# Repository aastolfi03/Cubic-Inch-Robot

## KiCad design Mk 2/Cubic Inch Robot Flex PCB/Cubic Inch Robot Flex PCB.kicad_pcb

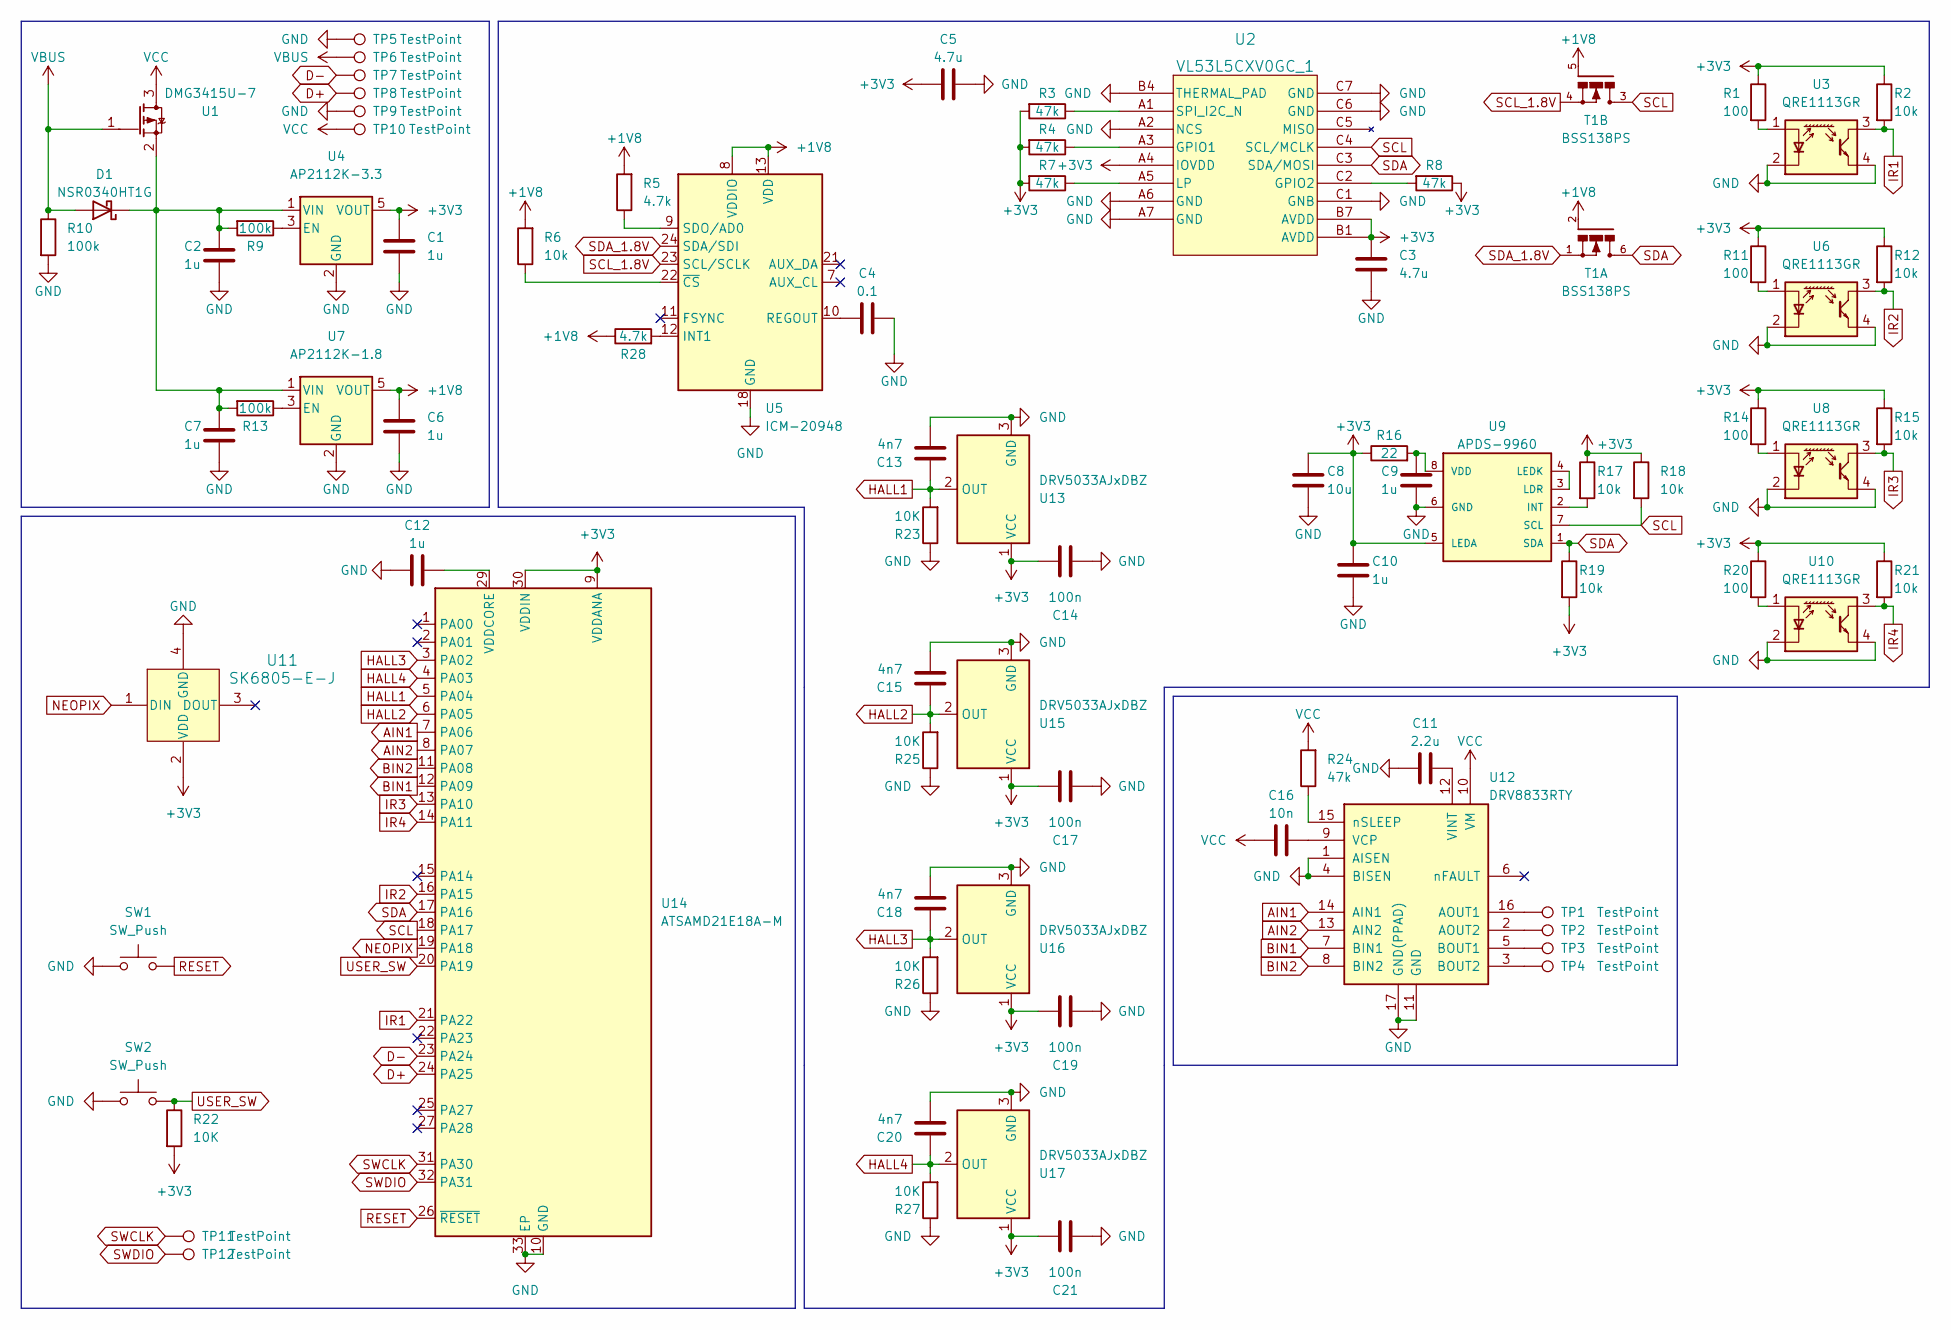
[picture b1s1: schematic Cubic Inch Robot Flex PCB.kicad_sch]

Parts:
C1, C2, C6, C7, C9, C10, C12: 1u; C_0603_1608Metric
C3, C5: 4.7u; C_0603_1608Metric
C4: 0.1; C_0603_1608Metric
C8: 10u; C_0603_1608Metric
C11: 2.2u; C_0603_1608Metric
C13, C15, C18, C20: 4n7; C_0603_1608Metric
C14, C17, C19, C21: 100n; C_0603_1608Metric
C16: 10n; C_0603_1608Metric
D1: NSR0340HT1G; D_SOD-323
R1, R11, R14, R20: 100; R_0603_1608Metric
R2, R6, R12, R15, R17, R18, R19, R21: 10k; R_0603_1608Metric
R3, R4, R7, R8, R24: 47k; R_0603_1608Metric
R5, R28: 4.7k; R_0603_1608Metric
R9, R10, R13: 100k; R_0603_1608Metric
R16: 22; R_0603_1608Metric
R22, R23, R25, R26, R27: 10K; R_0603_1608Metric
SW1, SW2: SW_Push; SW_Push_SPST_NO_Alps_SKRK
T1: BSS138PS; SOT363
TP1, TP2, TP3, TP4, TP5, TP6, TP7, TP8, TP9, TP10, TP11, TP12: TestPoint; TestPoint_Pad_D1.0mm
U1: DMG3415U-7; SOT95P240X105-3N; MPN DMG3415U-7
U2: VL53L5CXV0GC_1; LGA_CXV0GC&slash_1_STM
U3, U6, U8, U10: QRE1113GR; OnSemi_CASE100CY
U4: AP2112K-3.3; SOT-23-5
U5: ICM-20948; InvenSense_QFN-24_3x3mm_P0.4mm
U7: AP2112K-1.8; SOT-23-5
U9: APDS-9960
U11: SK6805-E-J; 4492_ADA
U12: DRV8833RTY; Texas_S-PWQFN-N16_EP2.1x2.1mm_ThermalVias
U13, U15, U16, U17: DRV5033AJxDBZ; SOT-23
U14: ATSAMD21E18A-M; QFN-32-1EP_5x5mm_P0.5mm_EP3.6x3.6mm

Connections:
+1V8: C6.1, R5.2, R6.2, R28.1, T1.2, T1.5, U5.8 (VDDIO), U5.13 (VDD), U7.5 (VOUT)
+3V3: C1.1, C3.1, C5.1, C8.1, C10.1, C14.2, C17.2, C19.2, C21.2, R1.1, R2.1, R3.2, R4.2, R7.2, R8.1, R11.1, R12.1, R14.1, R15.1, R16.1, R17.1, R18.1, R19.2, R20.1, R21.1, R22.2, U2.A4 (IOVDD), U2.B1 (AVDD), U2.B7 (AVDD), U4.5 (VOUT), U9.5 (LEDA), U11.2 (VDD), U13.1 (VCC), U14.9 (VDDANA), U14.30 (VDDIN), U15.1 (VCC), U16.1 (VCC), U17.1 (VCC)
AIN1: U12.14 (AIN1), U14.7 (PA06)
AIN2: U12.13 (AIN2), U14.8 (PA07)
BIN1: U12.7 (BIN1), U14.12 (PA09)
BIN2: U12.8 (BIN2), U14.11 (PA08)
D+: TP8.1, U14.24 (PA25)
D-: TP7.1, U14.23 (PA24)
GND: C1.2, C2.2, C3.2, C4.2, C5.2, C6.2, C7.2, C8.2, C9.2, C10.2, C11.1, C12.1, C13.2, C14.1, C15.2, C17.1, C18.2, C19.1, C20.2, C21.1, R10.2, R23.1, R25.1, R26.1, R27.1, SW1.1, SW2.1, TP5.1, TP9.1, U2.A2 (NCS), U2.A6 (GND), U2.A7 (GND), U2.B4 (THERMAL_PAD), U2.C1 (GNB), U2.C6 (GND), U2.C7 (GND), U3.2 (K), U3.4, U4.2 (GND), U5.18 (GND), U5.20 (GND), U6.2 (K), U6.4, U7.2 (GND), U8.2 (K), U8.4, U9.6 (GND), U10.2 (K), U10.4, U11.4 (GND), U12.1 (AISEN), U12.4 (BISEN), U12.11 (GND), U12.17 (GND(PPAD)), U13.3 (GND), U14.10 (GND), U14.28 (GND), U14.33 (EP), U15.3 (GND), U16.3 (GND), U17.3 (GND)
HALL1: C13.1, R23.2, U13.2 (OUT), U14.5 (PA04)
HALL2: C15.1, R25.2, U14.6 (PA05), U15.2 (OUT)
HALL3: C18.1, R26.2, U14.3 (PA02), U16.2 (OUT)
HALL4: C20.1, R27.2, U14.4 (PA03), U17.2 (OUT)
IR1: R2.2, U3.3, U14.21 (PA22)
IR2: R12.2, U6.3, U14.16 (PA15)
IR3: R15.2, U8.3, U14.13 (PA10)
IR4: R21.2, U10.3, U14.14 (PA11)
NEOPIX: U11.1 (DIN), U14.19 (PA18)
unnamed: C2.1, C7.1, D1.1 (K), R9.2, R13.2, U1.2, U4.1 (VIN), U7.1 (VIN)
unnamed: C4.1, U5.10 (REGOUT)
unnamed: C9.1, R16.2, U9.8 (VDD)
unnamed: C11.2, U12.12 (VINT)
unnamed: C12.2, U14.29 (VDDCORE)
unnamed: C16.2, U12.9 (VCP)
unnamed: R1.2, U3.1 (A)
unnamed: R3.1, U2.A1 (SPI_I2C_N)
unnamed: R4.1, U2.A3 (GPIO1)
unnamed: R5.1, U5.9 (SDO/AD0)
unnamed: R6.1, U5.22 (~CS)
unnamed: R7.1, U2.A5 (LP)
unnamed: R8.2, U2.C2 (GPIO2)
unnamed: R9.1, U4.3 (EN)
unnamed: R11.2, U6.1 (A)
unnamed: R13.1, U7.3 (EN)
unnamed: R14.2, U8.1 (A)
unnamed: R17.2, U9.2 (INT)
unnamed: R20.2, U10.1 (A)
unnamed: R24.1, U12.15 (nSLEEP)
unnamed: R28.2, U5.12 (INT1)
unnamed: TP1.1, U12.16 (AOUT1)
unnamed: TP2.1, U12.2 (AOUT2)
unnamed: TP3.1, U12.5 (BOUT1)
unnamed: TP4.1, U12.3 (BOUT2)
unnamed: U9.3 (LDR), U9.4 (LEDK)
RESET: SW1.2, U14.26 (~RESET)
SCL: R18.2, T1.3, U2.C4 (SCL/MCLK), U9.7 (SCL), U14.18 (PA17)
SCL_1.8V: T1.4, U5.23 (SCL/SCLK)
SDA: R19.1, T1.6, U2.C3 (SDA/MOSI), U9.1 (SDA), U14.17 (PA16)
SDA_1.8V: T1.1, U5.24 (SDA/SDI)
SWCLK: TP11.1, U14.31 (PA30)
SWDIO: TP12.1, U14.32 (PA31)
USER_SW: R22.1, SW2.2, U14.20 (PA19)
VBUS: D1.2 (A), R10.1, TP6.1, U1.1
VCC: C16.1, R24.2, TP10.1, U1.3, U12.10 (VM)

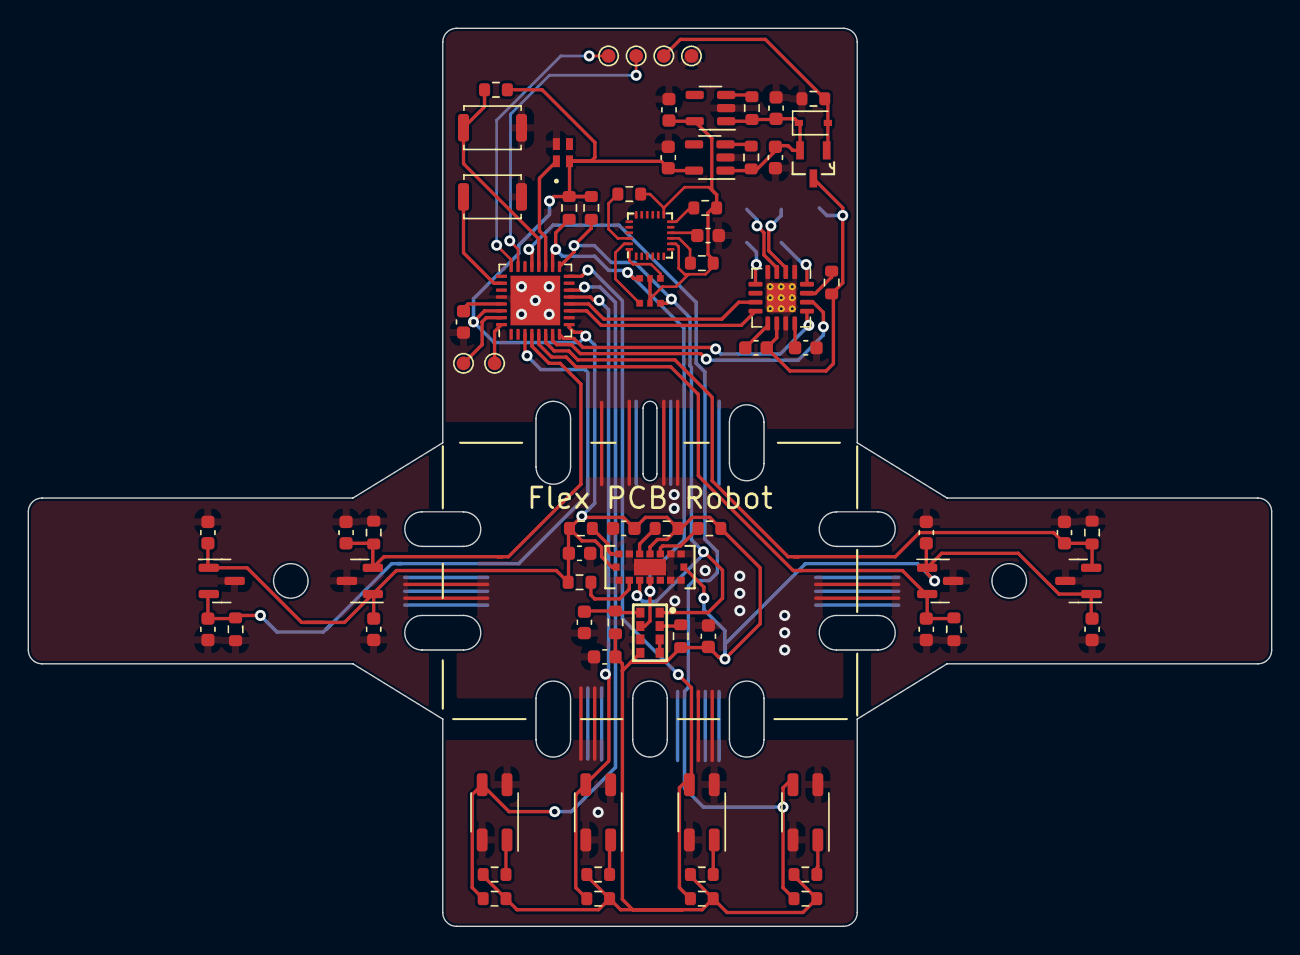
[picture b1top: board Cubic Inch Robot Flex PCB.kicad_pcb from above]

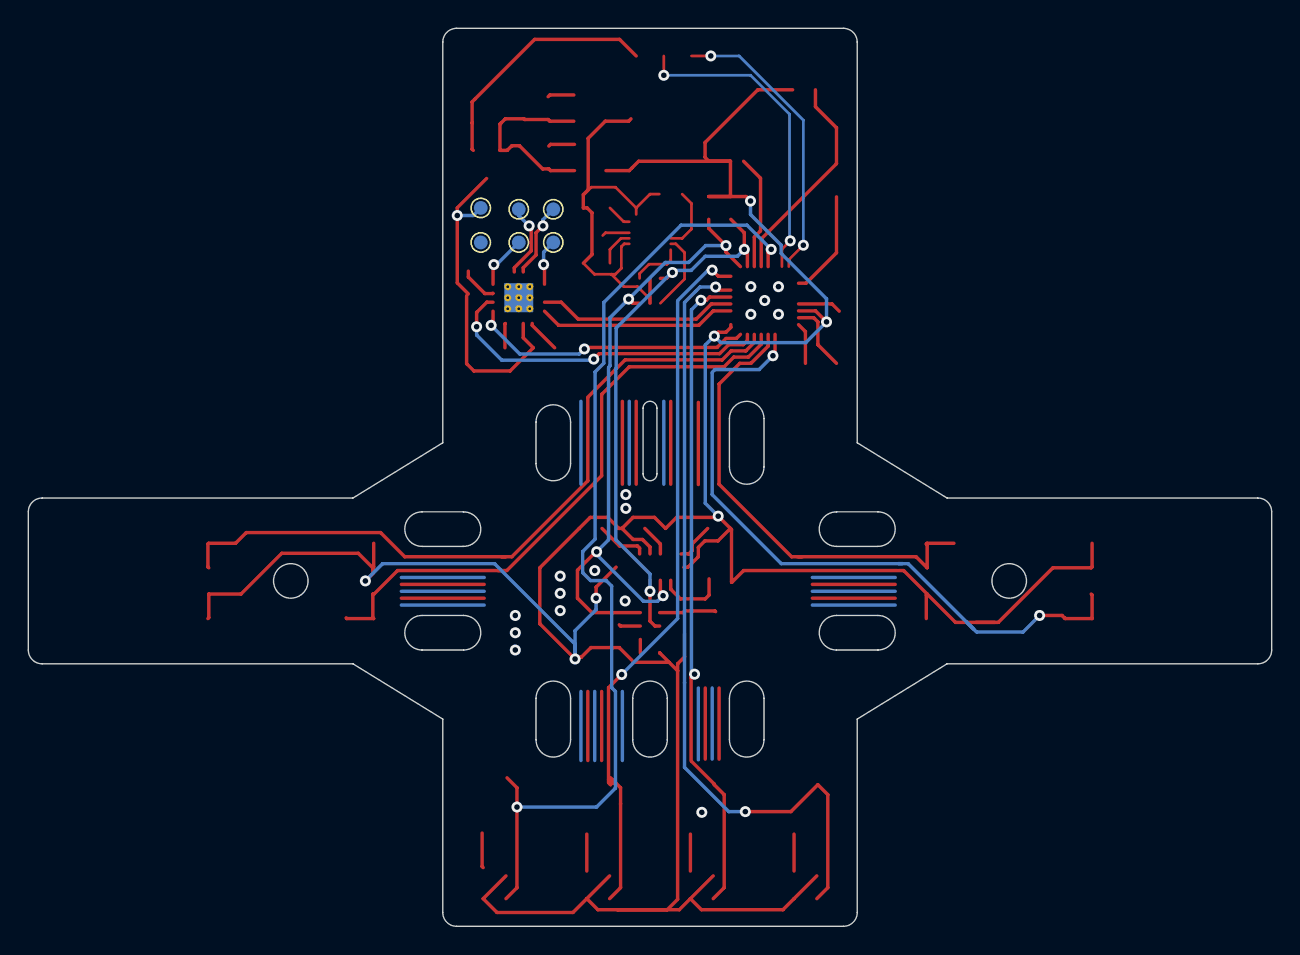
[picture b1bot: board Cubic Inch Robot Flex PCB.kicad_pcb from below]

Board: 2 copper layers, 90.0 x 65.0 mm, 82 parts (6 on the bottom side), 54 nets.

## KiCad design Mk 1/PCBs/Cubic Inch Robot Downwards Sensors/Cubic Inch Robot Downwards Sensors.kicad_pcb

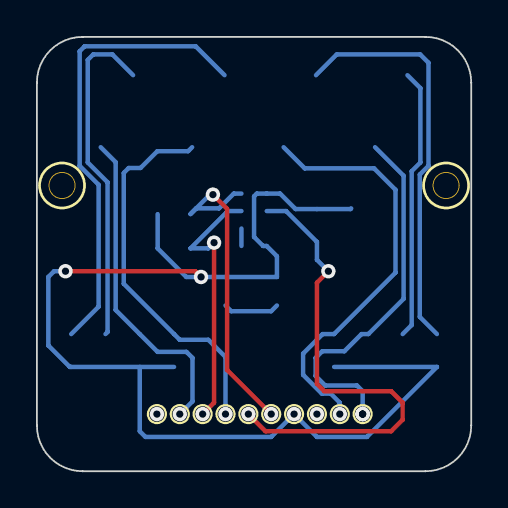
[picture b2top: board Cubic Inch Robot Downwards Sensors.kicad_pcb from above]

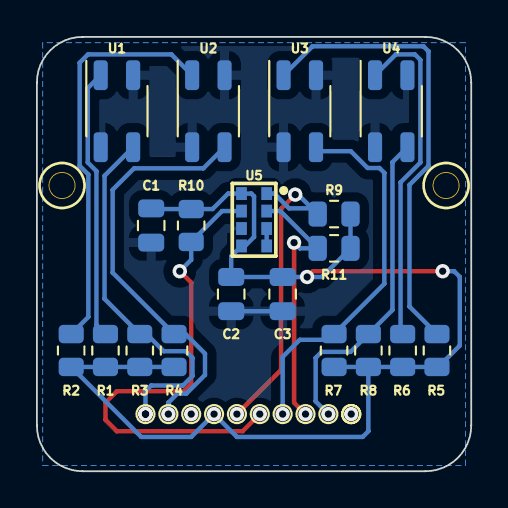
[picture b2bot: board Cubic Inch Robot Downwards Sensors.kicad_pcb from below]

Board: 2 copper layers, 24.1 x 24.1 mm, 30 parts (29 on the bottom side), 14 nets.

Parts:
C1: 50u; C_0805_2012Metric
C2, C3: 1u; C_0805_2012Metric
J1, J2, J3, J4, J5, J6, J7, J8, J8#2, J8#3, J9: Conn_01x01; TestPoint_Pad_D1.0mm
R1, R2, R5, R6: 100; R_0805_2012Metric
R3, R4, R7, R8, R9, R10, R11: 10k; R_0805_2012Metric
U1, U2, U3, U4: QRE1113GR; OnSemi_CASE100CY
U5: APDS-9960

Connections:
D2: J1.1, R11.1, U5.2 (INT)
D3: J2.1, R8.2, U4.3
D6: J5.1, R7.2, U3.3
D9: J6.1, R3.2, U1.3
D10: J7.1, R4.2, U2.3
GND: C1.1, C2.2, C3.1, J9.1, U1.2 (K), U1.4, U2.2 (K), U2.4, U3.2 (K), U3.4, U4.2 (K), U4.4, U5.6 (GND)
unnamed: R1.2, U1.1 (A)
unnamed: R2.2, U2.1 (A)
unnamed: R5.2, U3.1 (A)
unnamed: R6.2, U4.1 (A)
unnamed: U5.3 (LDR), U5.4 (LEDK)
SCL: J4.1, R10.1, U5.7 (SCL)
SDA: J3.1, R9.1, U5.1 (SDA)
VCC: C1.2, C2.1, C3.2, J8#2.1, R1.1, R2.1, R3.1, R4.1, R5.1, R6.1, R7.1, R8.1, R9.2, R10.2, R11.2, U5.5 (LEDA), U5.8 (VDD)

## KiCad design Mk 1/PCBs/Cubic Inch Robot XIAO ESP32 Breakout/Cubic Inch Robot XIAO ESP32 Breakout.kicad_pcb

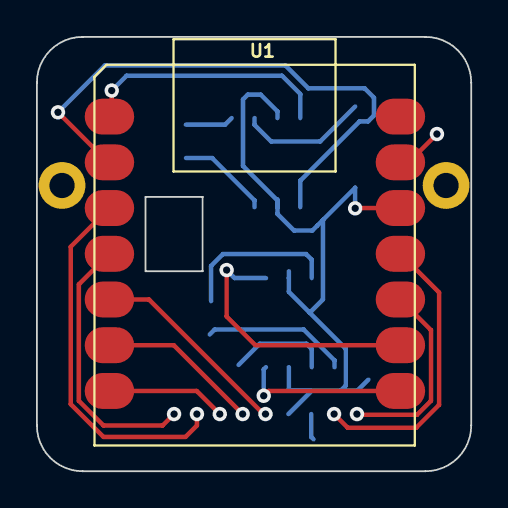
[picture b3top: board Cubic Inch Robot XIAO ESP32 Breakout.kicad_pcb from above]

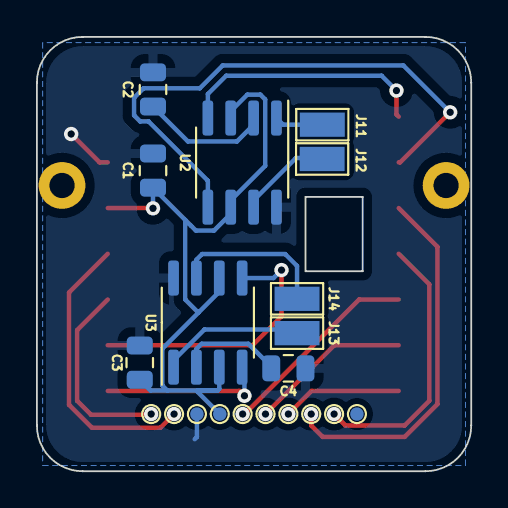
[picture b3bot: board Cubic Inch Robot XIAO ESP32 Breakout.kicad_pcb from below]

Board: 2 copper layers, 24.1 x 24.1 mm, 21 parts (20 on the bottom side), 19 nets.

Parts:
C1, C3: 1u; C_0805_2012Metric
C2, C4: 100n; C_0805_2012Metric
J2, J2#2, J3, J4, J5, J6, J7, J8, J9, J10: Conn_01x01; TestPoint_Pad_D0.75mm
J11, J12, J13, J14: Conn_01x01; TestPoint_Pad_1.5x1.5mm
U1: MOUDLE-SEEEDUINO-XIAO-ESP32S3; MOUDLE14P-SMD-2.54-21X17.8MM
U2, U3: ZXBM5210-S; SOIC-8_3.9x4.9mm_P1.27mm

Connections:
D0: U1.1 (PA02_A0_D0), U2.4 (FWD)
D1: U1.2 (PA4_A1_D1), U2.5 (REV)
D2: J2#2.1, U1.3 (PA10_A2_D2)
D3: J3.1, U1.4 (PA11_A3_D3)
D6: J6.1, U1.7 (PB08_A6_D6_TX)
D7: U1.8 (PB09_A7_D7_RX), U3.4 (FWD)
D8: U1.9 (PA7_A8_D8_SCK), U3.5 (REV)
D9: J7.1, U1.10 (PA5_A9_D9_MISO)
D10: J8.1, U1.11 (PA6_A10_D10_MOSI)
GND: C1.1, C2.1, C3.1, C4.1, J10.1, U1.13 (GND), U2.8 (GND), U3.8 (GND)
unnamed: C2.2, U2.2 (VM)
unnamed: C4.2, U3.2 (VM)
unnamed: J11.1, U2.1 (OUT1)
unnamed: J12.1, U2.7 (OUT2)
unnamed: J13.1, U3.1 (OUT1)
unnamed: J14.1, U3.7 (OUT2)
SCL: J5.1, U1.6 (PA9_A5_D5_SCL)
SDA: J4.1, U1.5 (PA8_A4_D4_SDA)
VCC: C1.2, C3.2, J9.1, U1.12 (3V3), U2.3 (VDD), U2.6 (VREF), U3.3 (VDD), U3.6 (VREF)

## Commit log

2024-01-12 EVERTHYING
